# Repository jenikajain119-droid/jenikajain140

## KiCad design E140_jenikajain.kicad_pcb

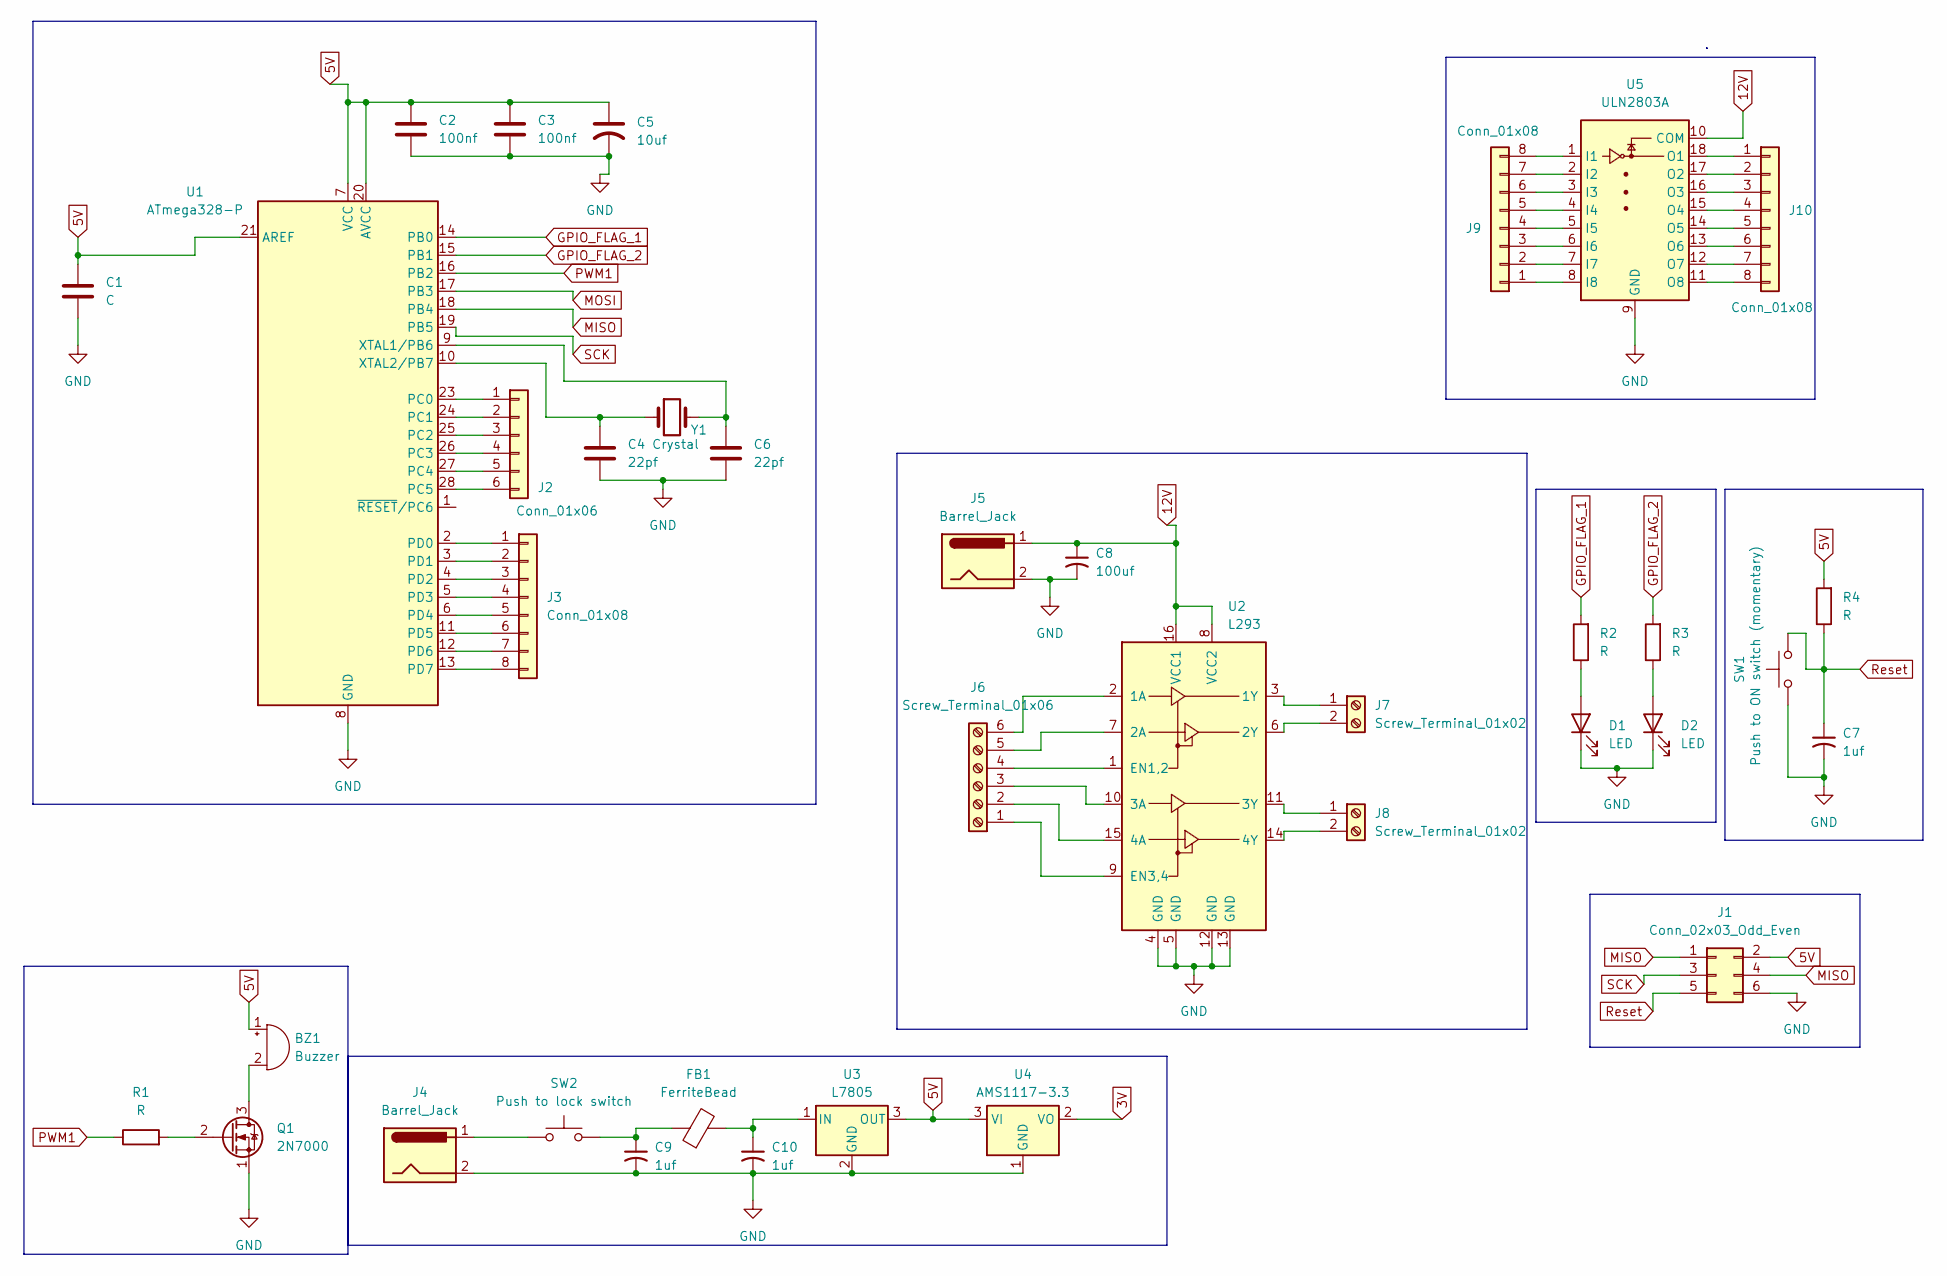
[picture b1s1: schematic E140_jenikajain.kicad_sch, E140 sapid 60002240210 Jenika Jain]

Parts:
BZ1: Buzzer; Buzzer_12x9.5RM7.6
C1: C; C_Disc_D7.0mm_W2.5mm_P5.00mm
C2, C3: 100nf; C_Disc_D7.0mm_W2.5mm_P5.00mm
C4, C6: 22pf; C_Disc_D7.0mm_W2.5mm_P5.00mm
C5: 10uf; C_Disc_D7.0mm_W2.5mm_P5.00mm
C7, C9, C10: 1uf; C_Disc_D7.0mm_W2.5mm_P5.00mm
C8: 100uf; C_Disc_D7.0mm_W2.5mm_P5.00mm
D1, D2: LED; LED_D8.0mm
FB1: FerriteBead; LairdTech_28C0236-0JW-10
J1: Conn_02x03_Odd_Even; PinHeader_2x03_P2.54mm_Vertical
J2: Conn_01x06; PinHeader_1x06_P2.54mm_Vertical
J3, J9, J10: Conn_01x08; PinHeader_1x08_P2.54mm_Vertical
J4, J5: Barrel_Jack; BarrelJack_CUI_PJ-063AH_Horizontal
J6: Screw_Terminal_01x06; TerminalBlock_MaiXu_MX126-5.0-06P_1x06_P5.00mm
J7, J8: Screw_Terminal_01x02; TerminalBlock_MaiXu_MX126-5.0-02P_1x02_P5.00mm
Q1: 2N7000; TO-92_Inline
R1, R2, R3, R4: R; R_Axial_DIN0207_L6.3mm_D2.5mm_P7.62mm_Horizontal
SW1: Push to ON switch (momentary); KSA_Tactile_SPST
SW2: Push to lock switch; KSA_Tactile_SPST
U1: ATmega328-P; DIP-28_W7.62mm
U2: L293; DIP-16_W7.62mm
U3: L7805; TO-220-3_Vertical
U4: AMS1117-3.3; SOT-223-3_TabPin2
U5: ULN2803A; DIP-18_W7.62mm
Y1: Crystal; Crystal_C26-LF_D2.1mm_L6.5mm_Vertical

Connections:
3V: U4.2 (VO)
5V: BZ1.1 (+), C1.1, C2.1, C3.1, C5.1, J1.2, R4.2, U1.7 (VCC), U1.20 (AVCC), U1.21 (AREF), U3.3 (OUT), U4.3 (VI)
12V: C8.1, J5.1, U2.8 (VCC2), U2.16 (VCC1), U5.10 (COM)
GND: C1.2, C2.2, C3.2, C4.2, C5.2, C6.2, C7.2, C8.2, C9.2, C10.2, D1.1 (K), D2.1 (K), J1.6, J4.2, J5.2, Q1.1 (S), SW1.1, U1.8 (GND), U1.22 (GND), U2.4 (GND), U2.5 (GND), U2.12 (GND), U2.13 (GND), U3.2 (GND), U4.1 (GND), U5.9 (GND)
GPIO_FLAG_1: R2.2, U1.14 (PB0)
GPIO_FLAG_2: R3.2, U1.15 (PB1)
MISO: J1.1, J1.4, U1.18 (PB4)
MOSI: U1.17 (PB3)
unnamed: BZ1.2 (-), Q1.3 (D)
unnamed: C9.1, FB1.1, SW2.2
unnamed: D1.2 (A), R2.1
unnamed: D2.2 (A), R3.1
unnamed: J2.1, U1.23 (PC0)
unnamed: J2.2, U1.24 (PC1)
unnamed: J2.3, U1.25 (PC2)
unnamed: J2.4, U1.26 (PC3)
unnamed: J2.5, U1.27 (PC4)
unnamed: J2.6, U1.28 (PC5)
unnamed: J3.1, U1.2 (PD0)
unnamed: J3.2, U1.3 (PD1)
unnamed: J3.3, U1.4 (PD2)
unnamed: J3.4, U1.5 (PD3)
unnamed: J3.5, U1.6 (PD4)
unnamed: J3.6, U1.11 (PD5)
unnamed: J3.7, U1.12 (PD6)
unnamed: J3.8, U1.13 (PD7)
unnamed: J4.1, SW2.1
unnamed: J6.1, U2.9 (EN3,4)
unnamed: J6.2, U2.15 (4A)
unnamed: J6.3, U2.10 (3A)
unnamed: J6.4, U2.1 (EN1,2)
unnamed: J6.5, U2.7 (2A)
unnamed: J6.6, U2.2 (1A)
unnamed: J7.1, U2.3 (1Y)
unnamed: J7.2, U2.6 (2Y)
unnamed: J8.1, U2.11 (3Y)
unnamed: J8.2, U2.14 (4Y)
unnamed: J9.1, U5.8 (I8)
unnamed: J9.2, U5.7 (I7)
unnamed: J9.3, U5.6 (I6)
unnamed: J9.4, U5.5 (I5)
unnamed: J9.5, U5.4 (I4)
unnamed: J9.6, U5.3 (I3)
unnamed: J9.7, U5.2 (I2)
unnamed: J9.8, U5.1 (I1)
unnamed: J10.1, U5.18 (O1)
unnamed: J10.2, U5.17 (O2)
unnamed: J10.3, U5.16 (O3)
unnamed: J10.4, U5.15 (O4)
unnamed: J10.5, U5.14 (O5)
unnamed: J10.6, U5.13 (O6)
unnamed: J10.7, U5.12 (O7)
unnamed: J10.8, U5.11 (O8)
unnamed: Q1.2 (G), R1.2
unnamed: C6.1, U1.9 (XTAL1/PB6), Y1.2
unnamed: C4.1, U1.10 (XTAL2/PB7), Y1.1
unnamed: C10.1, FB1.2, U3.1 (IN)
PWM1: R1.1, U1.16 (PB2)
Reset: C7.1, J1.5, R4.1, SW1.2
SCK: J1.3, U1.19 (PB5)

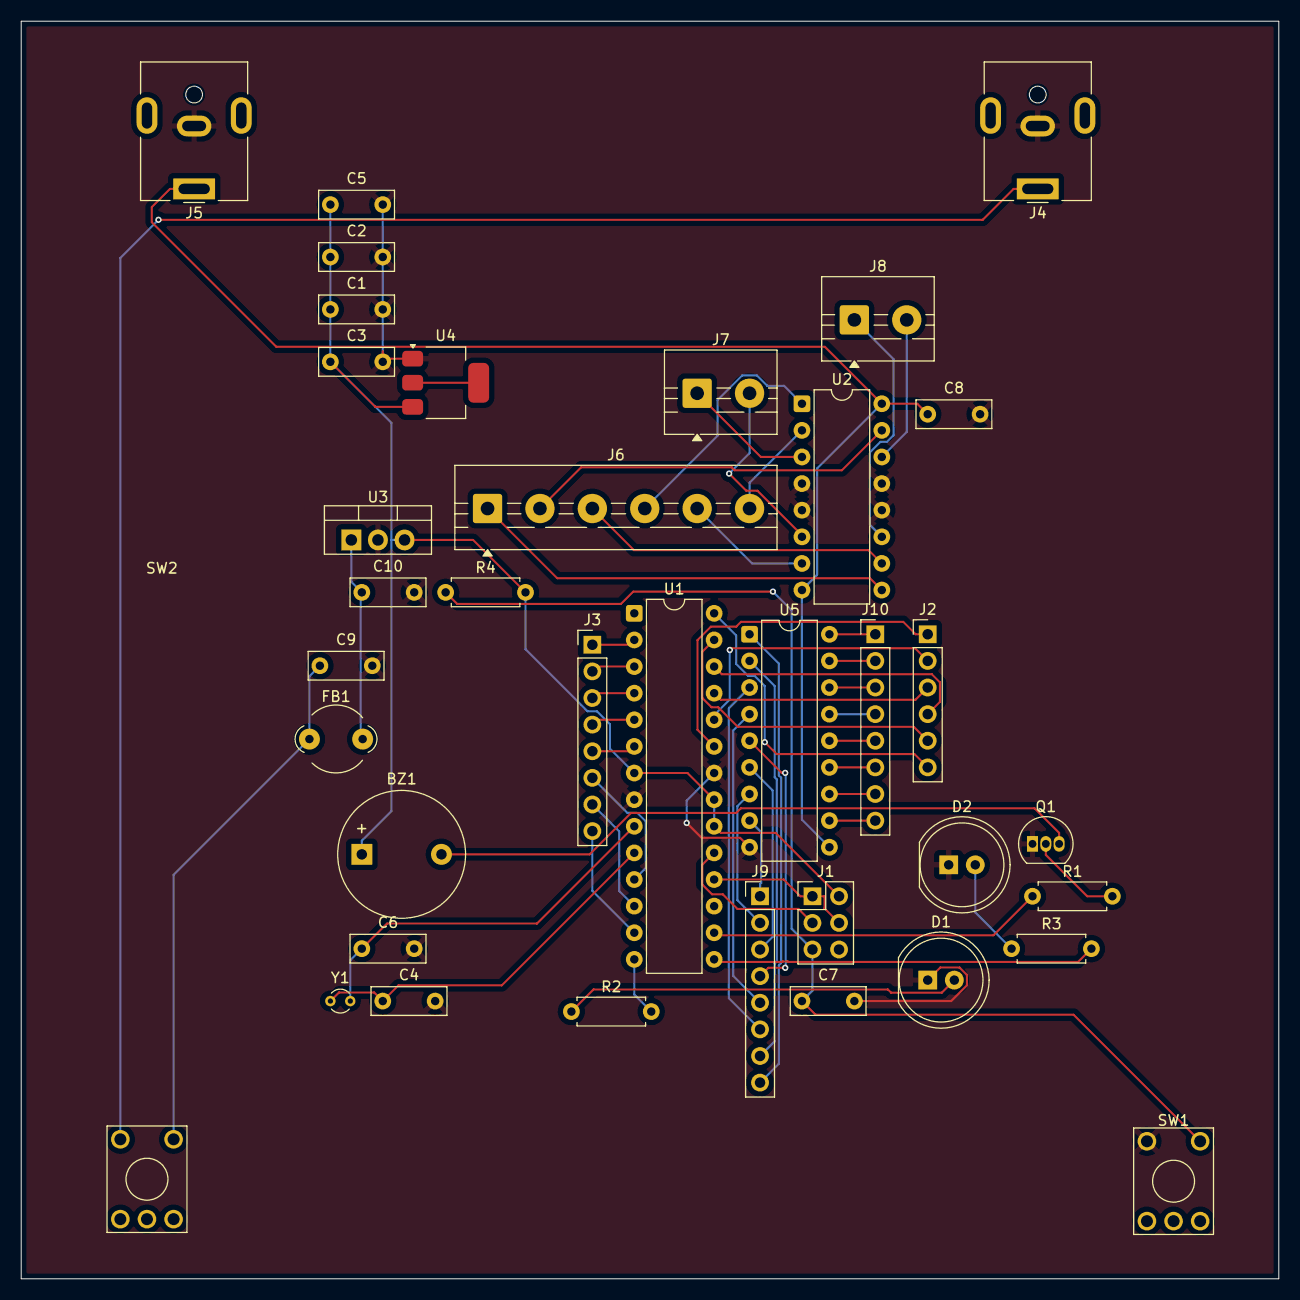
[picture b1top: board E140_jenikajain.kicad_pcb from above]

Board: 2 copper layers, 120.0 x 120.0 mm, 37 parts (0 on the bottom side), 58 nets.
